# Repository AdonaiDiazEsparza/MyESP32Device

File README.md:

# MyESP32Device

### Project Description

This project is a small development board design based on the **ESP32-C3 Super Mini**. Created for learning and experimentation, this board is optimized for interacting with wireless protocols such as **Wi-Fi, Bluetooth, and BLE**.

**Note:** This is, for now, only a concept and a design. The board has not been physically developed or manufactured.

---

### Key Features

- **ESP32-C3 Super Mini:** A powerful microcontroller ideal for IoT and security projects.
- **Expandable SPI Connectivity:** Includes a dedicated pinout to connect SPI devices, though it supports only one additional device in parallel due to a single chip select (SS) pin.
- **Serial Communication:** **TX** and **RX** pins are available for serial communication.
- **I2C Connection:** **SCL** and **SDA** pins are directly connected to an OLED display, making data visualization easy.
- **User Control:** A **multi-way switch** (up, down, left, right, and center) provides intuitive interaction with the board.

---

### Dimensions

- **35 mm x 40 mm**

---

### 3d Views

Here you can see the view of the board in 3d model.

---

### Usage

This board is ideal for:
- Automation and control projects that require a simple user interface.
- IoT prototyping and development.

---

### Author

- Adonai Diaz Esparza

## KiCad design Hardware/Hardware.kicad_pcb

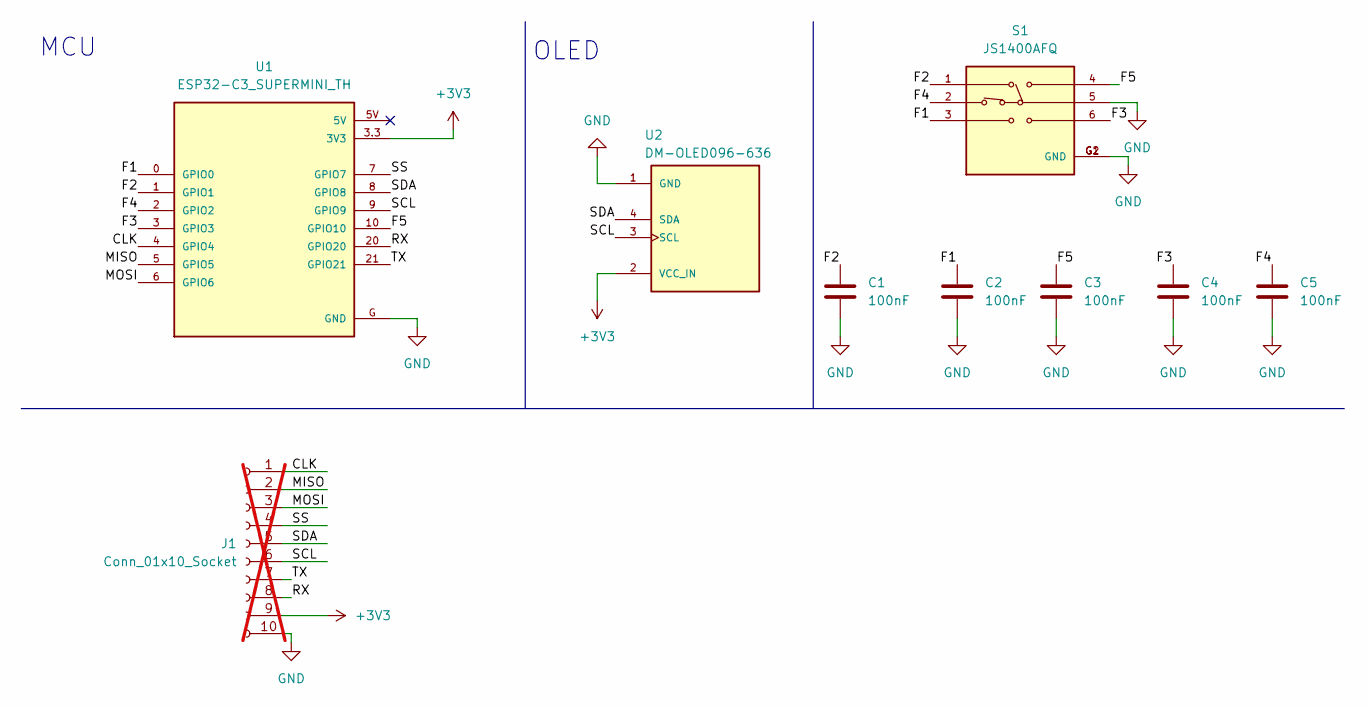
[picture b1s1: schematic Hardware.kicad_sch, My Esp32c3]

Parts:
C1, C2, C3, C4, C5: 100nF; C_0603_1608Metric_Pad1.08x0.95mm_HandSolder
J1: Conn_01x10_Socket; PinHeader_1x10_P2.54mm_Vertical; not fitted
S1: JS1400AFQ; SW_JS1400AFQ; PARTREV C
U1: ESP32-C3_SUPERMINI_TH; MODULE_ESP32-C3_SUPERMINI
U2: DM-OLED096-636; MODULE_DM-OLED096-636; PARTREV 2018-09-10

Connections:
+3V3: J1.9, U1.3.3 (3V3), U2.2 (VCC_IN)
/CLK: J1.1, U1.4 (GPIO4)
/F1: C2.1, S1.3, U1.0 (GPIO0)
/F2: C1.1, S1.1, U1.1 (GPIO1)
/F3: C4.1, S1.6, U1.3 (GPIO3)
/F4: C5.1, S1.2, U1.2 (GPIO2)
/F5: C3.1, S1.4, U1.10 (GPIO10)
/MISO: J1.2, U1.5 (GPIO5)
/MOSI: J1.3, U1.6 (GPIO6)
/RX: J1.8, U1.20 (GPIO20)
/SCL: J1.6, U1.9 (GPIO9), U2.3 (SCL)
/SDA: J1.5, U1.8 (GPIO8), U2.4 (SDA)
/SS: J1.4, U1.7 (GPIO7)
/TX: J1.7, U1.21 (GPIO21)
GND: C1.2, C2.2, C3.2, C4.2, C5.2, J1.10, S1.5, S1.G1 (GND), S1.G2 (GND), U1.G (GND), U2.1 (GND)

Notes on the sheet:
OLED
MCU

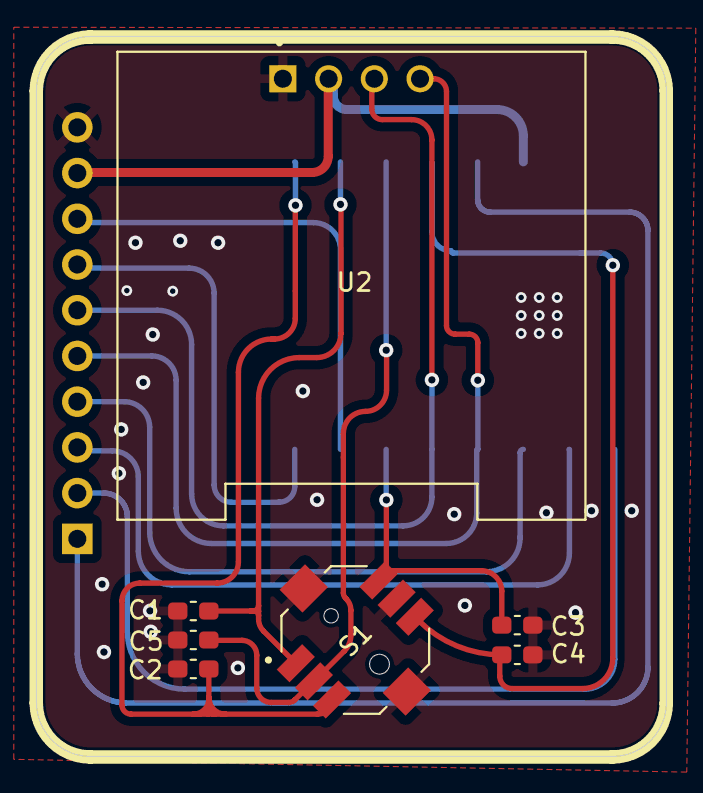
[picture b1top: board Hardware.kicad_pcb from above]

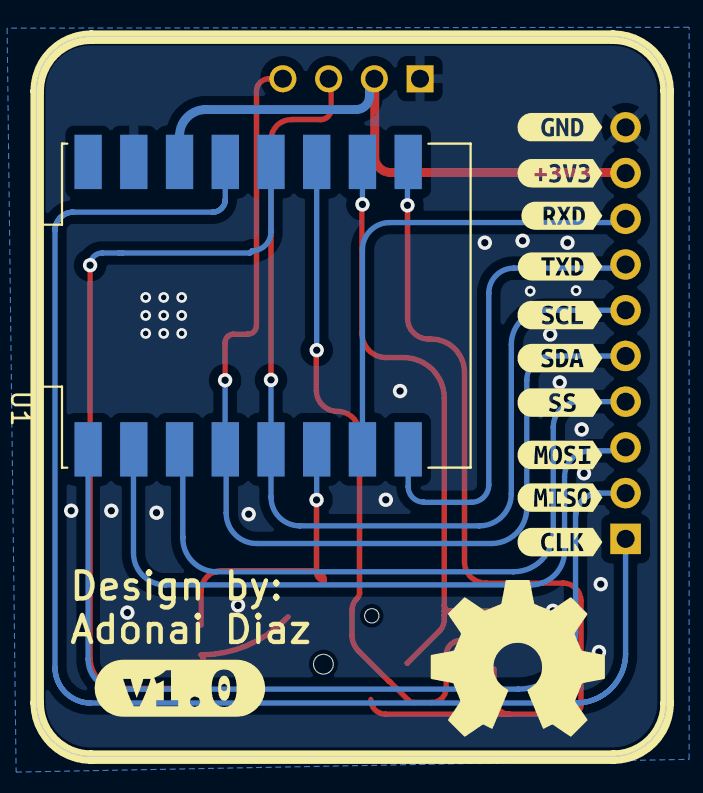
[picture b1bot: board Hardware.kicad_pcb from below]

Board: 2 copper layers, 35.0 x 40.0 mm, 20 parts (12 on the bottom side), 15 nets.

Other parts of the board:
kibuzzard-6891AAE2: G***; kibuzzard-6891AAE2
kibuzzard-6891AB0F: G***; kibuzzard-6891AB0F
kibuzzard-6891AB3F: G***; kibuzzard-6891AB3F
kibuzzard-6891AB4C: G***; kibuzzard-6891AB4C
kibuzzard-6891AB20: G***; kibuzzard-6891AB20
kibuzzard-6891AB27: G***; kibuzzard-6891AB27
kibuzzard-6891AB30: G***; kibuzzard-6891AB30
kibuzzard-6891AB39: G***; kibuzzard-6891AB39
kibuzzard-6891AB44: G***; kibuzzard-6891AB44
kibuzzard-6891AB56: G***; kibuzzard-6891AB56
kibuzzard-689394AC: G***; kibuzzard-689394AC

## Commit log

2025-08-03 feat: add kicad project and gitignore
2025-08-03 feat: add symbols, footprints and 3d models
2025-08-04 feat: add schematic design
2025-08-04 feat: change esp model & add footprints
2025-08-05 feat: add routes
2025-08-06 feat: add 3d model on the button
2025-08-06 feat: add open hardware logo & version
2025-08-06 docs: add images
2025-08-06 feat: create README
2025-08-06 feat: update readme
2025-08-06 fix: image in readme
2025-08-06 feat: update gitignore
